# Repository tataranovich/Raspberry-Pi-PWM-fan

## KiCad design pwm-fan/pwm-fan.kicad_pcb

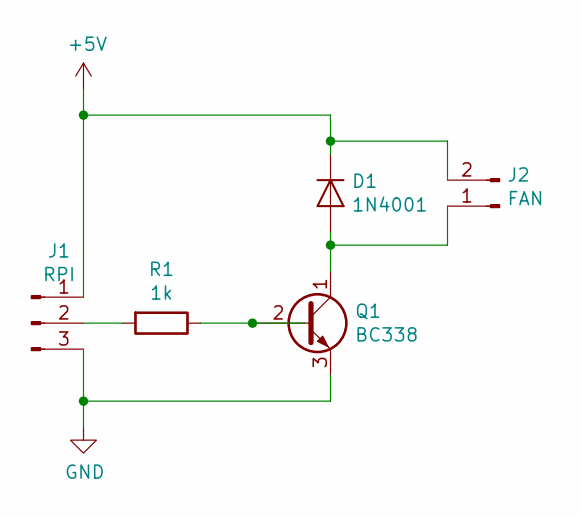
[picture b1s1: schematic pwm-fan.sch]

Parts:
D1: 1N4001; D_DO-41_SOD81_P10.16mm_Horizontal
J1: RPI; PinHeader_1x03_P2.54mm_Horizontal
J2: FAN; PinHeader_1x02_P2.54mm_Horizontal
Q1: BC338; TO-92_Inline
R1: 1k; R_Axial_DIN0207_L6.3mm_D2.5mm_P10.16mm_Horizontal

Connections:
unnamed: D1.1 (K), J1.1, J2.2
unnamed: D1.2 (A), J2.1, Q1.1 (C)
unnamed: J1.2, R1.2
unnamed: J1.3, Q1.3 (E)
unnamed: Q1.2 (B), R1.1

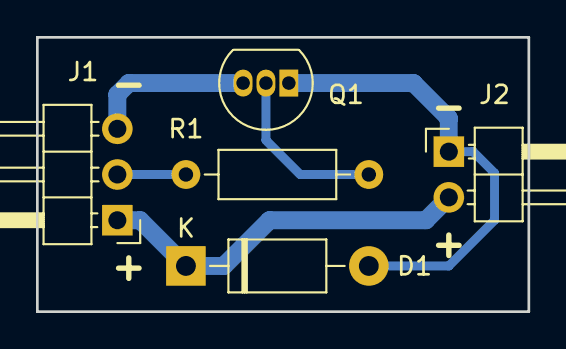
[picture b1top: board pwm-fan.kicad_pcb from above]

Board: 2 copper layers, 27.3 x 15.2 mm, 5 parts (0 on the bottom side), 5 nets.

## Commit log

2020-11-22 Cleanup code and adopt for LibreELEC
2020-11-22 Add signal handler and start fan at full speed.
2020-11-22 Add systemd service.
2020-11-25 Added Kicad project.
